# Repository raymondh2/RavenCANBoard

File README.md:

# ravencanboard
Your Pi CAN also have wings

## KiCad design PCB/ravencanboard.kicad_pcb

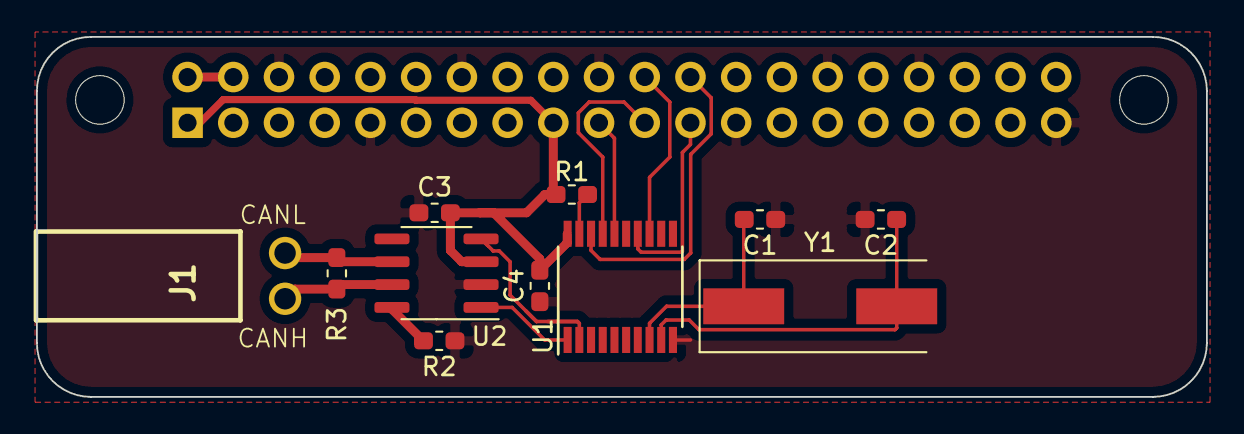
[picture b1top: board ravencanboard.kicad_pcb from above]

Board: 2 copper layers, 65.0 x 20.0 mm, 14 parts (1 on the bottom side), 16 nets.

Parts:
C1, C2: 22pF; C_0603_1608Metric_Pad1.05x0.95mm_HandSolder
C3, C4: .1uF; C_0603_1608Metric_Pad1.05x0.95mm_HandSolder
J1: 171857-0002
MK1, MK2: M2.5; MountingHole_2.7mm_M2.5
P1: Conn_02x20_Odd_Even; PinSocket_2x20_P2.54mm_Vertical
R1: 10K; R_0603_1608Metric_Pad1.05x0.95mm_HandSolder
R2: 1K; R_0603_1608Metric_Pad1.05x0.95mm_HandSolder
R3: 120; R_0603_1608Metric_Pad1.05x0.95mm_HandSolder
U1: MCP2515-xST; TSSOP-20_4.4x6.5mm_P0.65mm
U2: SN65HVD230; SOIC-8_3.9x4.9mm_P1.27mm
Y1: 8MHz; Crystal_SMD_HC49-SD

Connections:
+3V3: C3.2, C4.2, P1.1, P1.17, R1.2, U1.20, U2.3
+5V: P1.2, P1.4
/CANH: J1.1, R3.2, U2.7
/CANL: J1.2, R3.1, U2.6
/CANRX: U1.2, U2.4
/CANTX: U1.1, U2.1
/GPIO8(SPI0_CE_N): P1.24, U1.18
/GPIO9(SPI0_MISO): P1.21, U1.17
/GPIO10(SPI0_MOSI): P1.19, U1.16
/GPIO11(SPI0_SCK): P1.23, U1.14
/GPIO25(GEN6): P1.22, U1.13
GND: C1.1, C2.1, C3.1, C4.1, P1.6, P1.9, P1.14, P1.20, P1.25, P1.30, P1.34, P1.39, R2.1, U1.10, U2.2
unnamed: C1.2, U1.8, Y1.1
unnamed: C2.2, U1.9, Y1.2
unnamed: R1.1, U1.19
unnamed: R2.2, U2.8

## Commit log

2020-05-11 Saving progress
2020-05-11 First Layout
2020-05-11 Make one sided
2020-05-27 Recommit
2020-05-27 resize
2020-05-28 Revert size
